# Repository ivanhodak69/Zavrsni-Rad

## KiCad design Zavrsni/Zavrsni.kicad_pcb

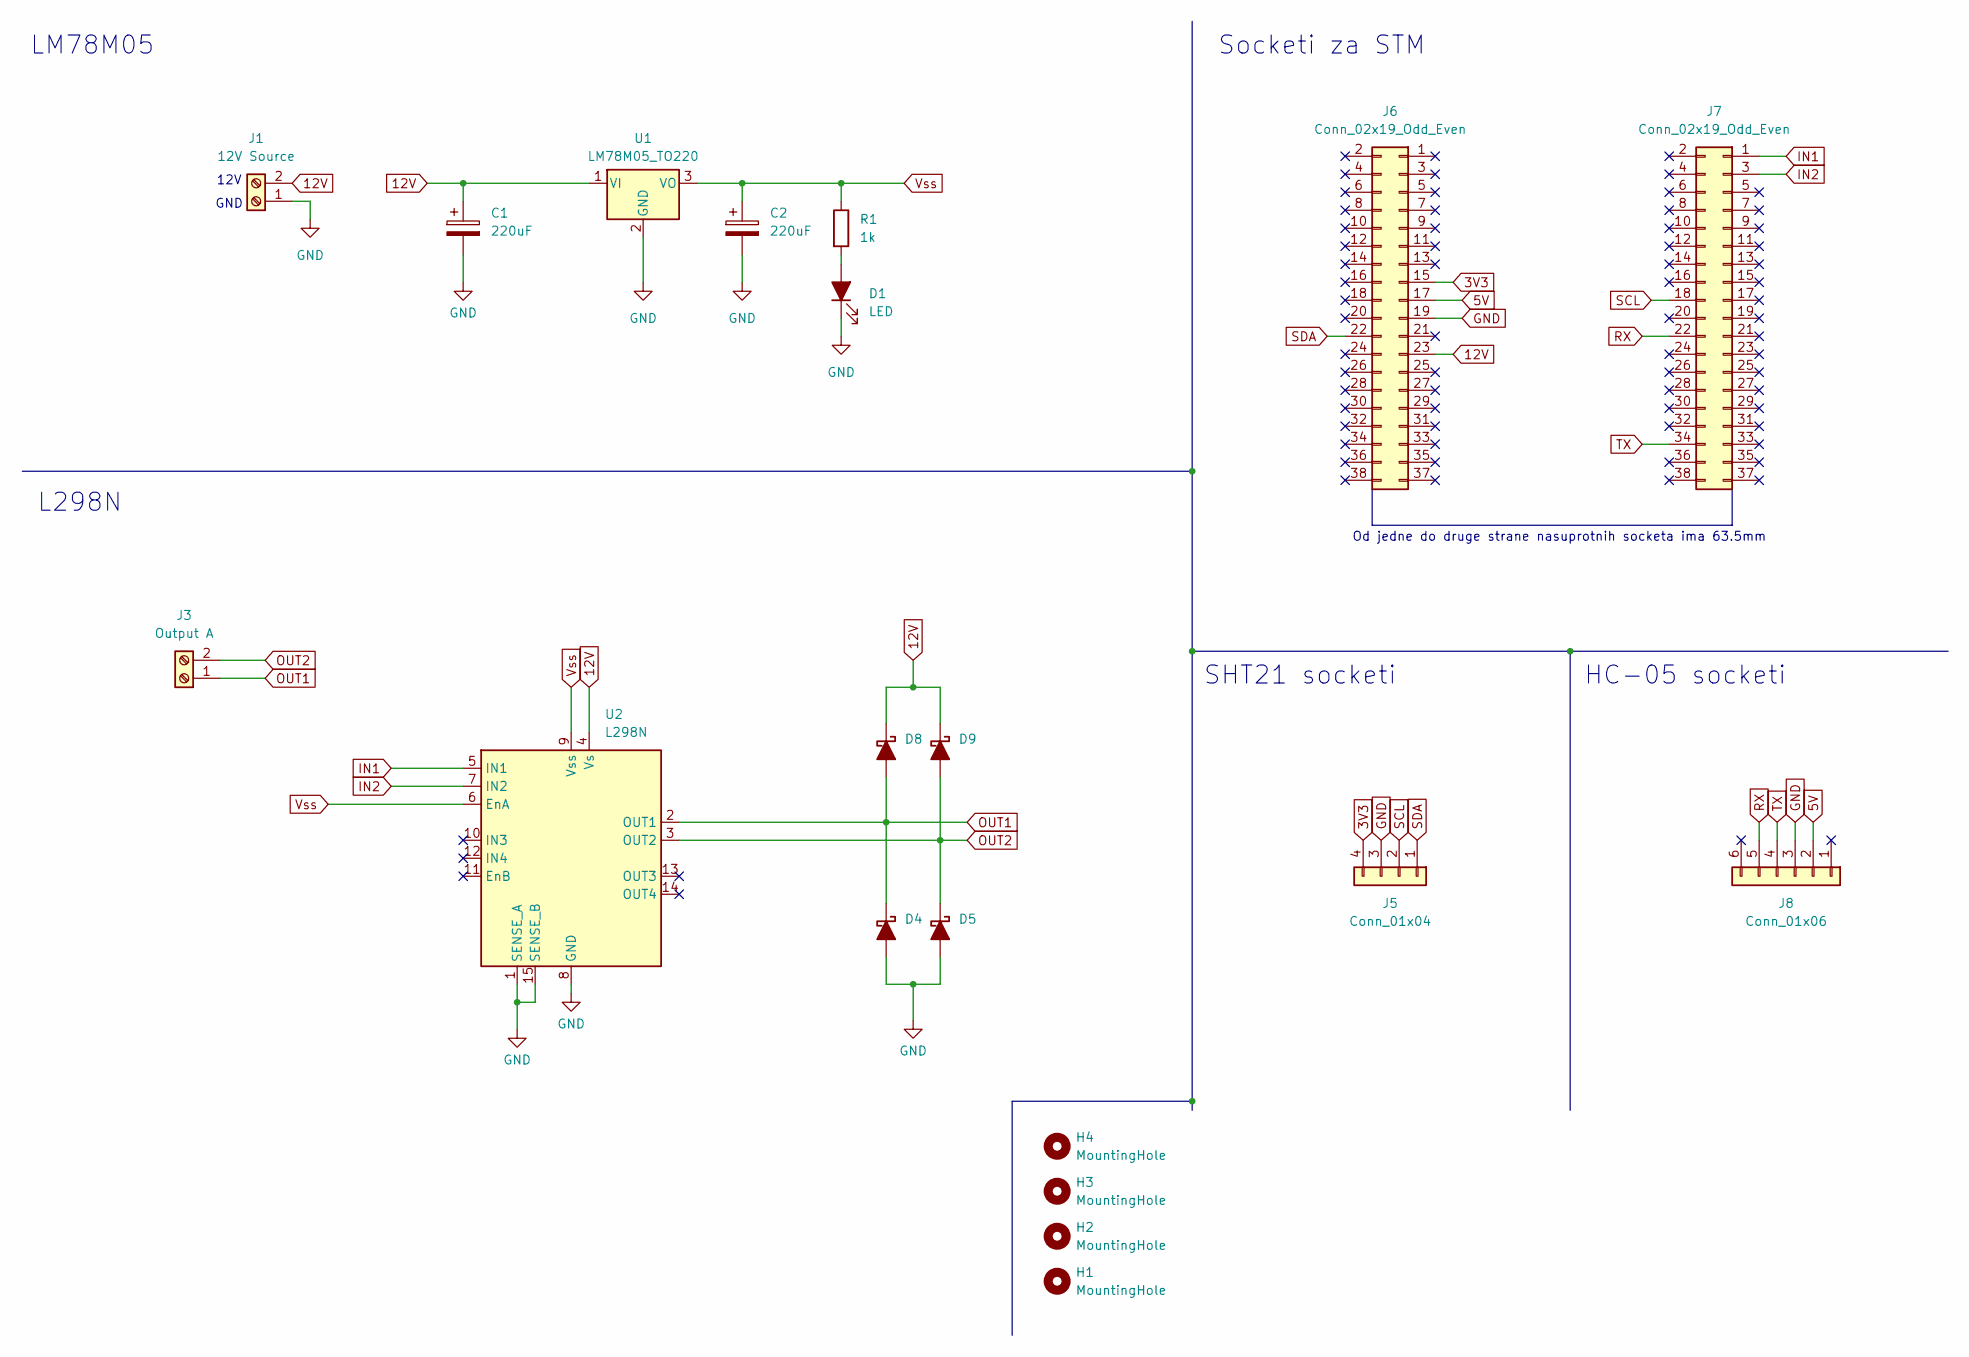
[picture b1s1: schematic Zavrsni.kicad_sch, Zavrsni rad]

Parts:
C1, C2: 220uF; CP_Radial_D5.0mm_P2.00mm
D1: LED; LED_D5.0mm
D4, D5, D8, D9: D_Schottky_Filled; D_DO-41_SOD81_P12.70mm_Horizontal
H1, H2, H3, H4: MountingHole; MountingHole_3mm
J1: 12V Source; TerminalBlock_Phoenix_MPT-0,5-2-2.54_1x02_P2.54mm_Horizontal
J3: Output A; TerminalBlock_Phoenix_MPT-0,5-2-2.54_1x02_P2.54mm_Horizontal
J5: Conn_01x04; PinSocket_1x04_P2.54mm_Vertical
J6, J7: Conn_02x19_Odd_Even; PinSocket_2x19_P2.54mm_Vertical
J8: Conn_01x06; PinSocket_1x06_P2.54mm_Vertical
R1: 1k; R_Axial_DIN0204_L3.6mm_D1.6mm_P5.08mm_Horizontal
U1: LM78M05_TO220; TO-220-3_Vertical; Manufacturer part number TO-220
U2: L298N; TO127P2020X500X2100-15; Manufacturer part number L298

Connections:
3V3: J5.4, J6.15
5V: J6.17, J8.2
12V: C1.1, D8.1 (K), D9.1 (K), J1.2, J6.23, U1.1 (VI), U2.4 (Vs)
GND: C1.2, C2.2, D1.1 (K), D4.2 (A), D5.2 (A), J1.1, J5.3, J6.19, J8.3, U1.2 (GND), U2.1 (SENSE_A), U2.8 (GND), U2.15 (SENSE_B)
GUMB: J7.5
IN1: J7.1, U2.5 (IN1)
IN2: J7.3, U2.7 (IN2)
unnamed: D1.2 (A), R1.2
OUT1: D4.1 (K), D8.2 (A), J3.1, U2.2 (OUT1)
OUT2: D5.1 (K), D9.2 (A), J3.2, U2.3 (OUT2)
RX: J7.22, J8.5
SCL: J5.2, J7.18
SDA: J5.1, J6.22
TX: J7.34, J8.4
Vss: C2.1, R1.1, U1.3 (VO), U2.6 (EnA), U2.9 (Vss)

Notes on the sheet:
GND
LM78M05
Od jedne do druge strane nasuprotnih socketa ima 63.5mm
SHT21 socketi
HC-05 socketi
12V
L298N
Socketi za STM

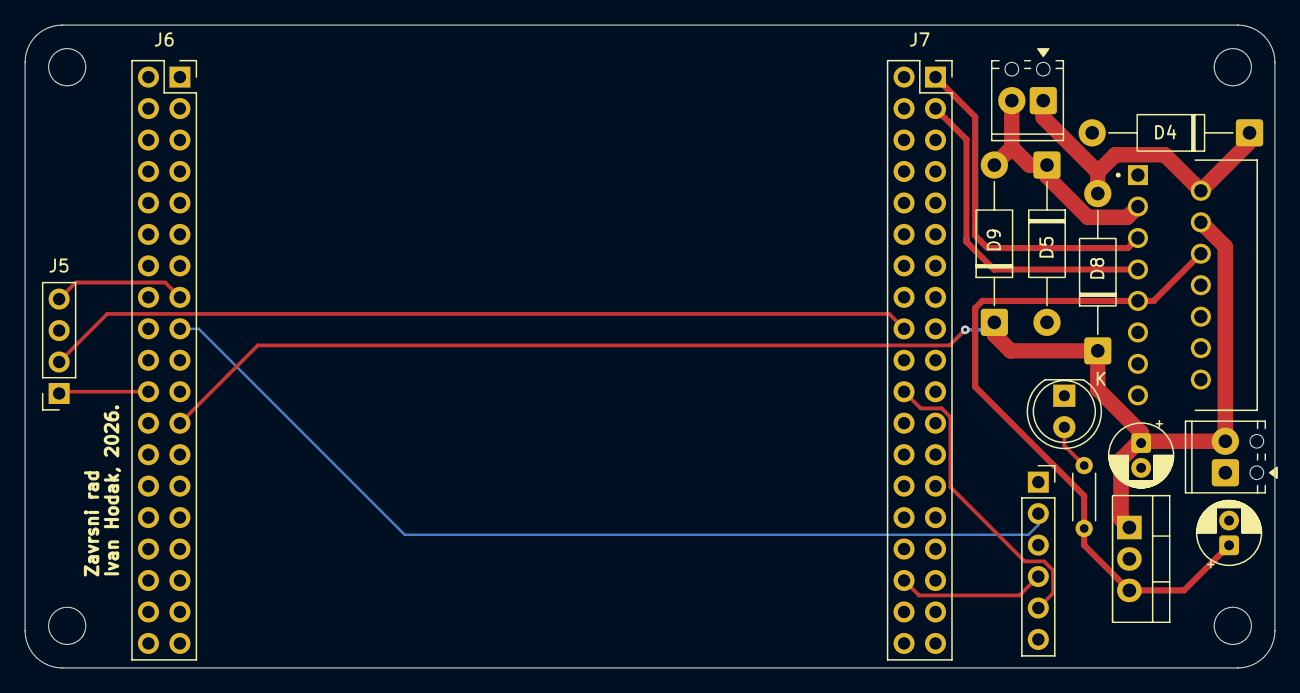
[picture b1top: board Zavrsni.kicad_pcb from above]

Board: 2 copper layers, 100.9 x 51.9 mm, 20 parts (0 on the bottom side), 14 nets.

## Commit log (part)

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2026-01-27 Link
2026-01-27 LM298N
2026-03-12 Big Update
2026-03-17 Plot
2026-04-17 New 3
2026-04-25 New 4
2026-05-06 Final
2026-05-11 Finale
